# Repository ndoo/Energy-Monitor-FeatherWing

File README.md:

# Energy Monitor FeatherWing

Eagle sources for an Energy Monitor FeatherWing PCB for Adafruit Feather M0 (ATSAMD21)

## Features

* 3 3.5mm jacks for current transformers (R3=R6=R9=22Ω burden resistor for YHDC SCT-013-000)
* 3 pairs of screw terminals (J1) (≤9VAC) for real power/power factor readings

## Software

An Arduino sketch that publishes MQTT feeds can be found at [ndoo/Energy-Monitor-ATSAMD21](https://github.com/ndoo/Energy-Monitor-ATSAMD21)

## Prerequisites/Caveats

* Designed for [Adafruit M0 Feather](https://www.adafruit.com/product/3010)
* Uses 6 analog pins (won't work with other Adafruit Feathers with fewer analog pins)
* Uses ATSAMD21 internal 12-bit ADC
* No built-in rectifier/regulator to power itself from 9VAC terminals
* Must be top FeatherWing in a stack as the TRS jacks obstruct some Feather pins

Note: While I have tried to use ≥10mil design rules, I may have left some 6mil tolerance parts in because Seeed Studios' Fusion PCB service has 6mil tolerances. If you use a different PCB fab, you should run an Eagle DRU check against your chosen fab's tolerances!

## BOM

### PCB BOM

* See "Seeed Fusion PCBA BOM.csv" for a CSV file that can be used with [Seeed Studio's Fusion PCBA service](https://www.seeedstudio.com/fusion_pcb.html)
* 2.54mm pin header strips: 16-pin + 4-pin
* 2.54mm screw terminal: 6-pin

### Transformers

* Current transformer:  YHDC SCT-013-000 100A split core current transformer ([OpenEnergyMonitor](http://shop.openenergymonitor.com/100a-max-clip-on-current-sensor-ct/) [Seeed Studio](https://www.seeedstudio.com/Noninvasive-AC-Current-Sensor-100A-max-p-547.html) [DX.com](http://www.dx.com/p/sct013-0-100a-non-invasive-ac-current-sensor-split-core-current-transformer-blue-359292))
* Voltage transformer:  Ideal Power 77DB-06-09 9VAC transformer ([OpenEnergyMonitor](https://shop.openenergymonitor.com/ac-ac-power-supply-adapter-ac-voltage-sensor-uk-plug/) [element14](http://sg.element14.com/ideal-power/77db-06-09/power-supply-ac-ac-10w-9v-0-67a/dp/2368014))

## Assembly

1. Solder SMD passives (I suggest using a PCBA service as I used 0402 parts)
 * If you solder the AC voltage divider wrongly, you may blow up the 0402 passives or destroy your Feather's LDO!
2. Solder 2.54mm screw terminal
3. Solder 2.54mm pin headers
4. Connect AC monitoring input(s)
5. Connect current transformer(s)
6. Configure and upload sketch to Feather M0
7. Stack FeatherWing and power up

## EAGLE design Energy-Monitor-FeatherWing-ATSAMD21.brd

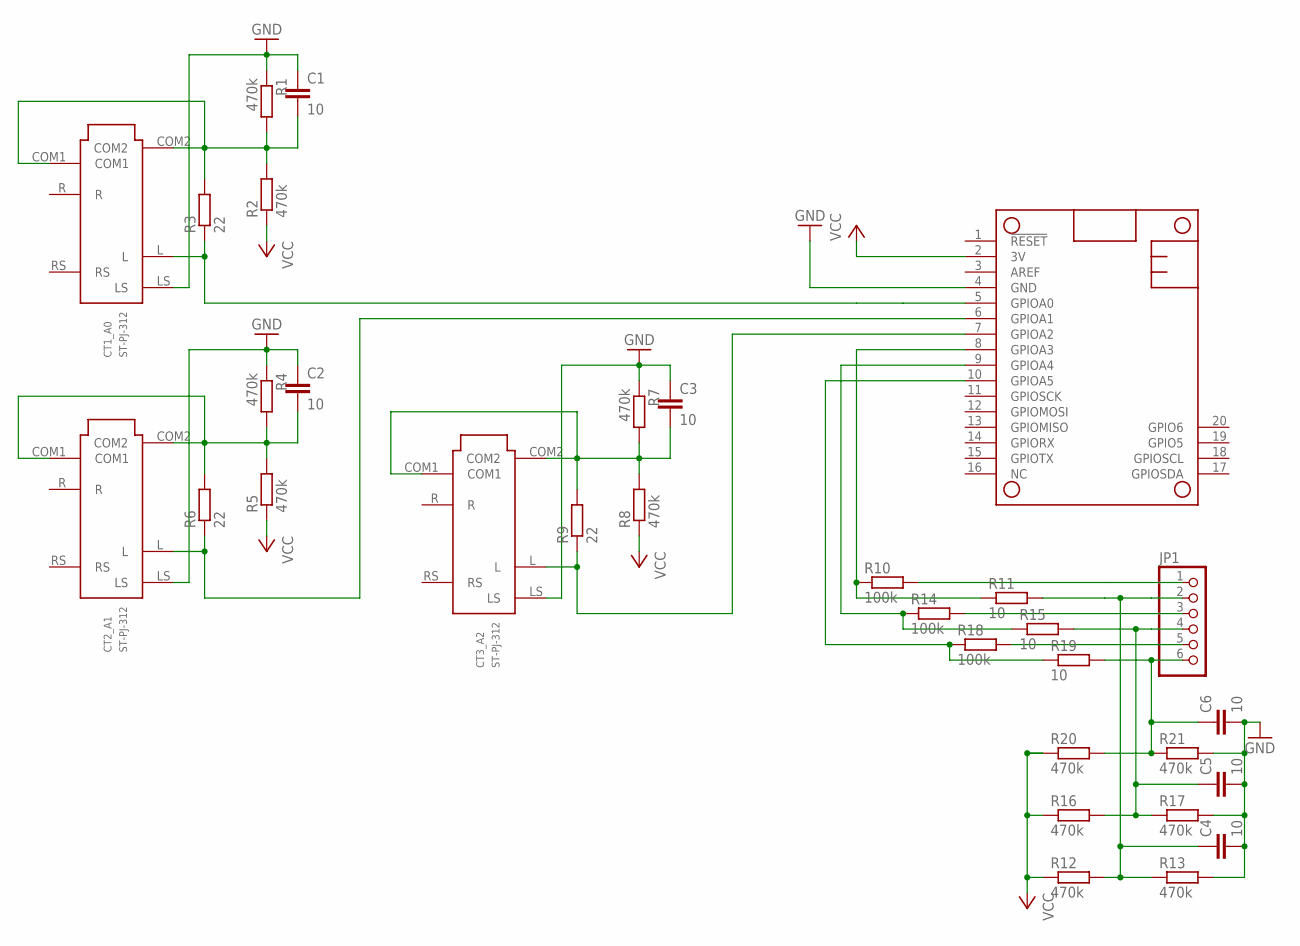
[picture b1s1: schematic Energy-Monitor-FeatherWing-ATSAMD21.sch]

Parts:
C1, C2, C3, C4, C5, C6: 10; C0402
CT1_A0, CT2_A1, CT3_A2: ST-PJ-312; SUNTECH_ST-PJ-312
JP1: PINHD-1X6CB; 1X06-CLEANBIG
MS1: FEATHERWING
R1, R2, R4, R5, R7, R8, R12, R13, R16, R17, R20, R21: 470k; R0402
R3, R6, R9: 22; R0402
R10, R14, R18: 100k; R0402
R11, R15, R19: 10; R0402

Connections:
AC_GND: C6.1, JP1.6, R19.2, R20.2, R21.1
CT1_REF: C1.2, CT1_A0.COM1, CT1_A0.COM2, R1.2, R2.2, R3.2
CT2_REF: C2.2, CT2_A1.COM1, CT2_A1.COM2, R4.2, R5.2, R6.2
CT3_REF: C3.2, CT3_A2.COM1, CT3_A2.COM2, R7.2, R8.2, R9.2
GND: C1.1, C2.1, C3.1, C4.2, C5.2, C6.2, CT1_A0.LS, CT2_A1.LS, CT3_A2.LS, MS1.4 (GND), R1.1, R4.1, R7.1, R13.2, R17.2, R21.2
unnamed: CT1_A0.L, MS1.5 (GPIOA0), R3.1
unnamed: CT2_A1.L, MS1.6 (GPIOA1), R6.1
unnamed: CT3_A2.L, MS1.7 (GPIOA2), R9.1
unnamed: JP1.1, R10.2
unnamed: MS1.8 (GPIOA3), R10.1, R11.1
unnamed: C5.1, JP1.4, R15.2, R16.2, R17.1
unnamed: JP1.3, R14.2
unnamed: MS1.9 (GPIOA4), R14.1, R15.1
unnamed: C4.1, JP1.2, R11.2, R12.2, R13.1
unnamed: JP1.5, R18.2
unnamed: MS1.10 (GPIOA5), R18.1, R19.1
VCC: MS1.2 (3V), R2.1, R5.1, R8.1, R12.1, R16.1, R20.1

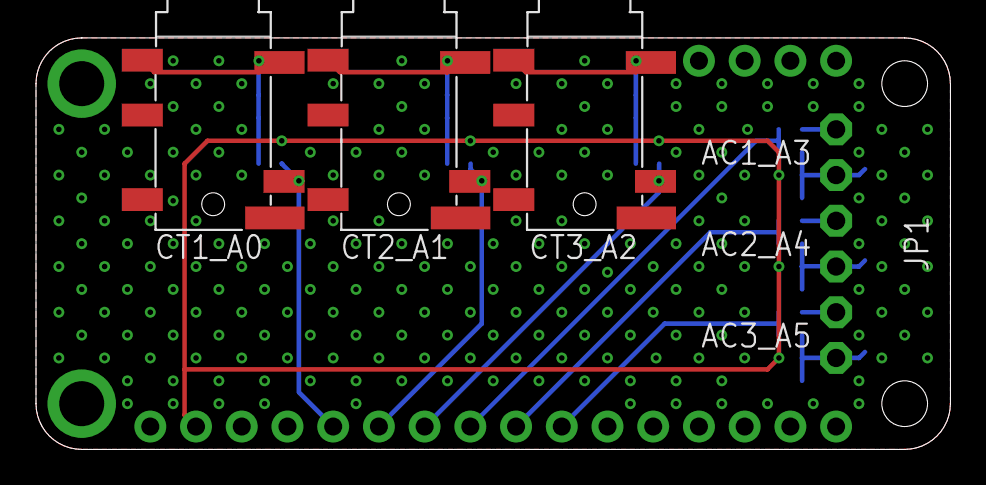
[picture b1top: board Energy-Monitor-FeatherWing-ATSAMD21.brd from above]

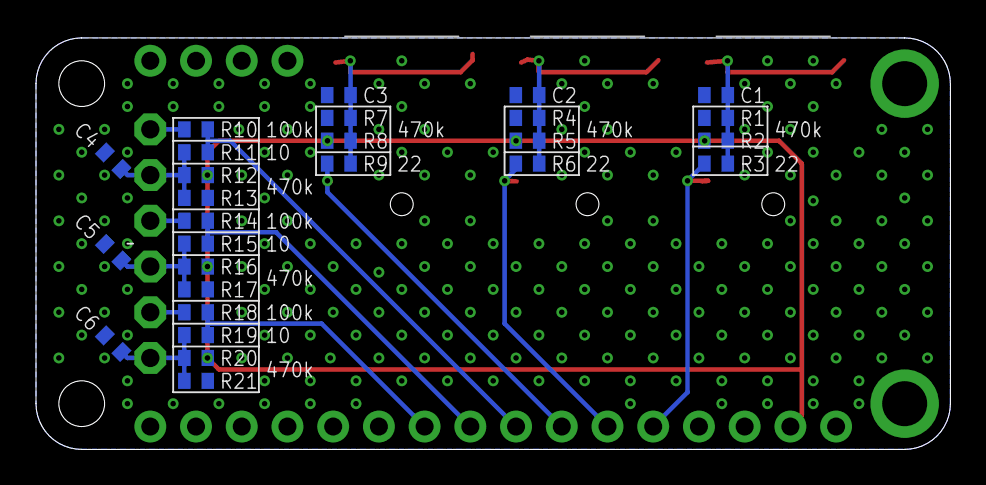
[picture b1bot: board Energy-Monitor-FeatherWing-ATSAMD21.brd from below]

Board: 2 copper layers, 50.8 x 22.9 mm, 32 parts (27 on the bottom side), 17 nets.

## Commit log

2016-08-28 Initial upload
2016-08-29 Clean up layout and component names
2016-08-29 Initial work on adding 3-phase bridge rectifier
2016-08-29 Add 3-phase bridge rectifier to BOM
2016-08-29 Mirror SDA006-7 to rear of board
2016-08-30 Fix layout issues - the TRS jacks have a rim that is not flush with the PCB, had to sacrifice some FeatherWing pins.
2016-08-31 Create LICENSE
2016-09-24 Better name silkscreen and more GND vias
2016-09-24 MIT license
2016-09-24 Layout cleanup; add hints for PCBA
2016-09-24 Remove vias too close to SMD headphone jack pads
2016-09-26 Rename files to match repository name
2016-09-26 Add BOM for Seeed Studio Fusion PCBA
2016-09-26 Update README.md with transformer BOM and 12VAC -> 9VAC
2016-09-26 Fix typo
2016-09-26 Fix typo and add magic smoke warning
2016-09-26 Update README.md - typo
2016-09-26 Update README.md with PCB 6mil warning
2016-09-26 Update README.md - remove vestigial 12VAC docs
